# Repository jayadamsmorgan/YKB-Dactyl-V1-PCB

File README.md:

# YKB Skadi KiCad PCB files

## Project setup

```bash
git clone https://github.com/jayadamsmorgan/ykb-skadi-pcb
cd ykb-skadi-pcb
git submodule init
git submodule update
```

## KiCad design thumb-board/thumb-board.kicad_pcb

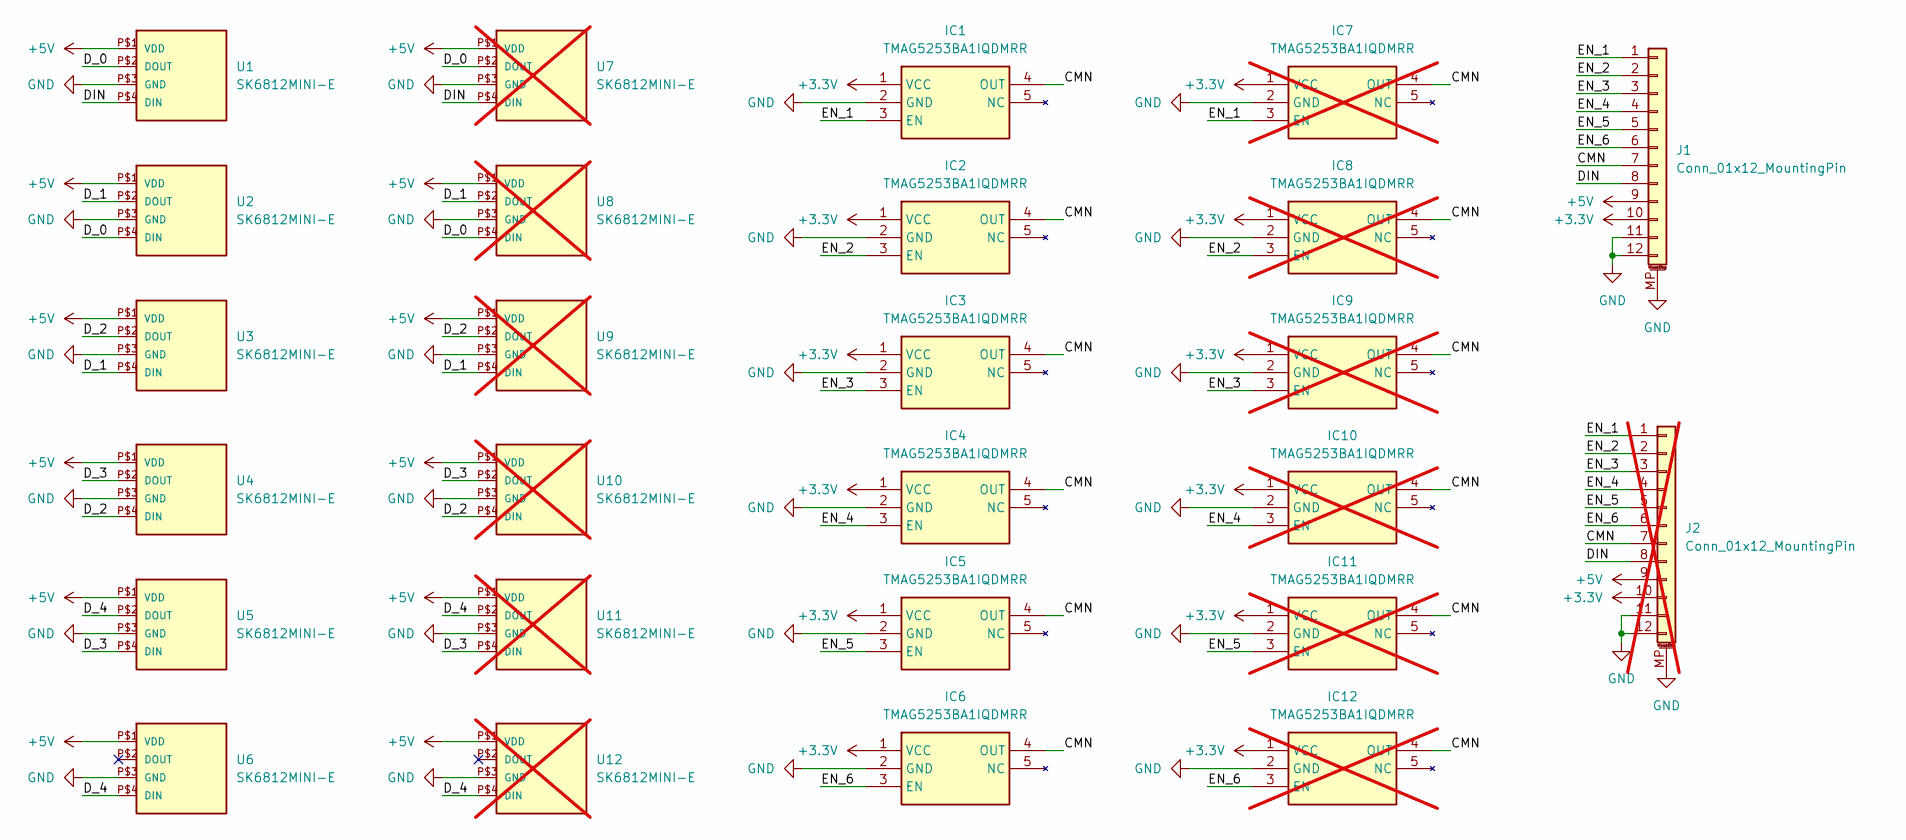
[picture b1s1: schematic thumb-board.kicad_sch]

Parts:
IC1, IC2, IC3, IC4, IC5, IC6: TMAG5253BA1IQDMRR; Mouser Part Number 595-TMAG5253BA1IQDMR
IC7, IC8, IC9, IC10, IC11, IC12: TMAG5253BA1IQDMRR; Mouser Part Number 595-TMAG5253BA1IQDMR; not fitted
J1: Conn_01x12_MountingPin; JST_SH_BM12B-SRSS-TB_1x12-1MP_P1.00mm_Vertical
J2: Conn_01x12_MountingPin; JST_SH_BM12B-SRSS-TB_1x12-1MP_P1.00mm_Vertical; not fitted
U1, U2, U3, U4, U5, U6: SK6812MINI-E
U7, U8, U9, U10, U11, U12: SK6812MINI-E; not fitted

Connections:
+3.3V: IC1.1 (VCC), IC2.1 (VCC), IC3.1 (VCC), IC4.1 (VCC), IC5.1 (VCC), IC6.1 (VCC), IC7.1 (VCC), IC8.1 (VCC), IC9.1 (VCC), IC10.1 (VCC), IC11.1 (VCC), IC12.1 (VCC), J1.10, J2.10
+5V: J1.9, J2.9, U1.P$1 (VDD), U2.P$1 (VDD), U3.P$1 (VDD), U4.P$1 (VDD), U5.P$1 (VDD), U6.P$1 (VDD), U7.P$1 (VDD), U8.P$1 (VDD), U9.P$1 (VDD), U10.P$1 (VDD), U11.P$1 (VDD), U12.P$1 (VDD)
/CMN: IC1.4 (OUT), IC2.4 (OUT), IC3.4 (OUT), IC4.4 (OUT), IC5.4 (OUT), IC6.4 (OUT), IC7.4 (OUT), IC8.4 (OUT), IC9.4 (OUT), IC10.4 (OUT), IC11.4 (OUT), IC12.4 (OUT), J1.7, J2.7
/DIN: J1.8, J2.8, U1.P$4 (DIN), U7.P$4 (DIN)
/D_0: U1.P$2 (DOUT), U2.P$4 (DIN), U7.P$2 (DOUT), U8.P$4 (DIN)
/D_1: U2.P$2 (DOUT), U3.P$4 (DIN), U8.P$2 (DOUT), U9.P$4 (DIN)
/D_2: U3.P$2 (DOUT), U4.P$4 (DIN), U9.P$2 (DOUT), U10.P$4 (DIN)
/D_3: U4.P$2 (DOUT), U5.P$4 (DIN), U10.P$2 (DOUT), U11.P$4 (DIN)
/D_4: U5.P$2 (DOUT), U6.P$4 (DIN), U11.P$2 (DOUT), U12.P$4 (DIN)
/EN_1: IC1.3 (EN), IC7.3 (EN), J1.1, J2.1
/EN_2: IC2.3 (EN), IC8.3 (EN), J1.2, J2.2
/EN_3: IC3.3 (EN), IC9.3 (EN), J1.3, J2.3
/EN_4: IC4.3 (EN), IC10.3 (EN), J1.4, J2.4
/EN_5: IC5.3 (EN), IC11.3 (EN), J1.5, J2.5
/EN_6: IC6.3 (EN), IC12.3 (EN), J1.6, J2.6
GND: IC1.2 (GND), IC2.2 (GND), IC3.2 (GND), IC4.2 (GND), IC5.2 (GND), IC6.2 (GND), IC7.2 (GND), IC8.2 (GND), IC9.2 (GND), IC10.2 (GND), IC11.2 (GND), IC12.2 (GND), J1.11, J1.12, J1.MP (MountPin), J2.11, J2.12, J2.MP (MountPin), U1.P$3 (GND), U2.P$3 (GND), U3.P$3 (GND), U4.P$3 (GND), U5.P$3 (GND), U6.P$3 (GND), U7.P$3 (GND), U8.P$3 (GND), U9.P$3 (GND), U10.P$3 (GND), U11.P$3 (GND), U12.P$3 (GND)

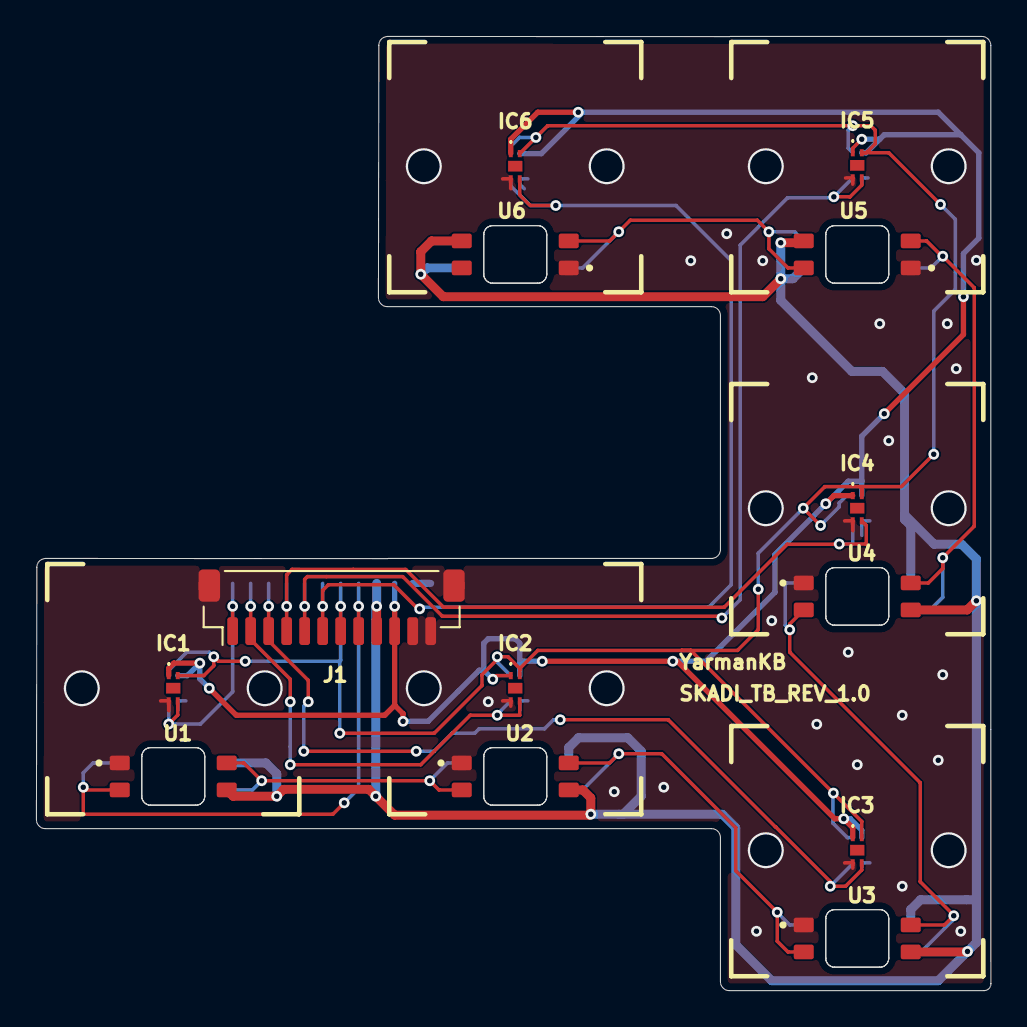
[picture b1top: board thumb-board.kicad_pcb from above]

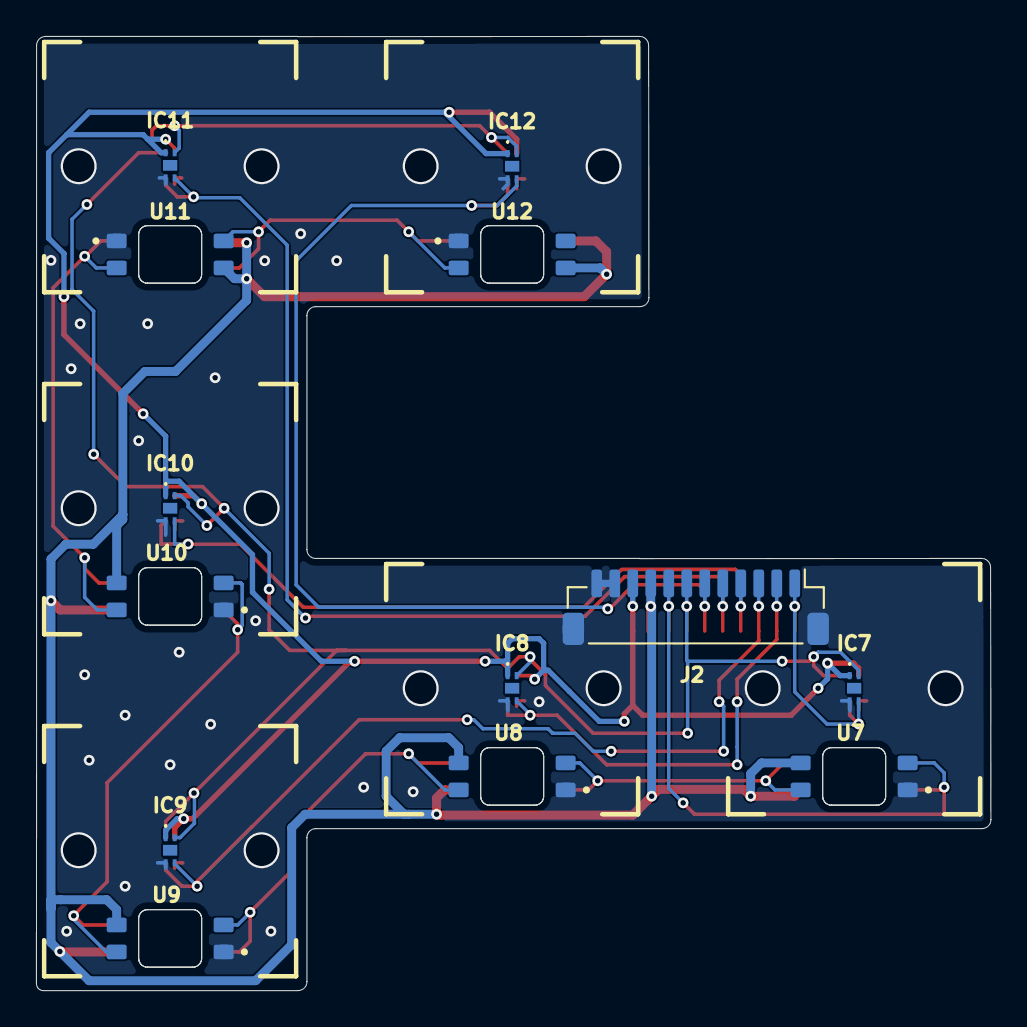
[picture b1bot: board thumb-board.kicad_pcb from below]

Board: 2 copper layers, 53.0 x 53.0 mm, 26 parts (13 on the bottom side), 16 nets.

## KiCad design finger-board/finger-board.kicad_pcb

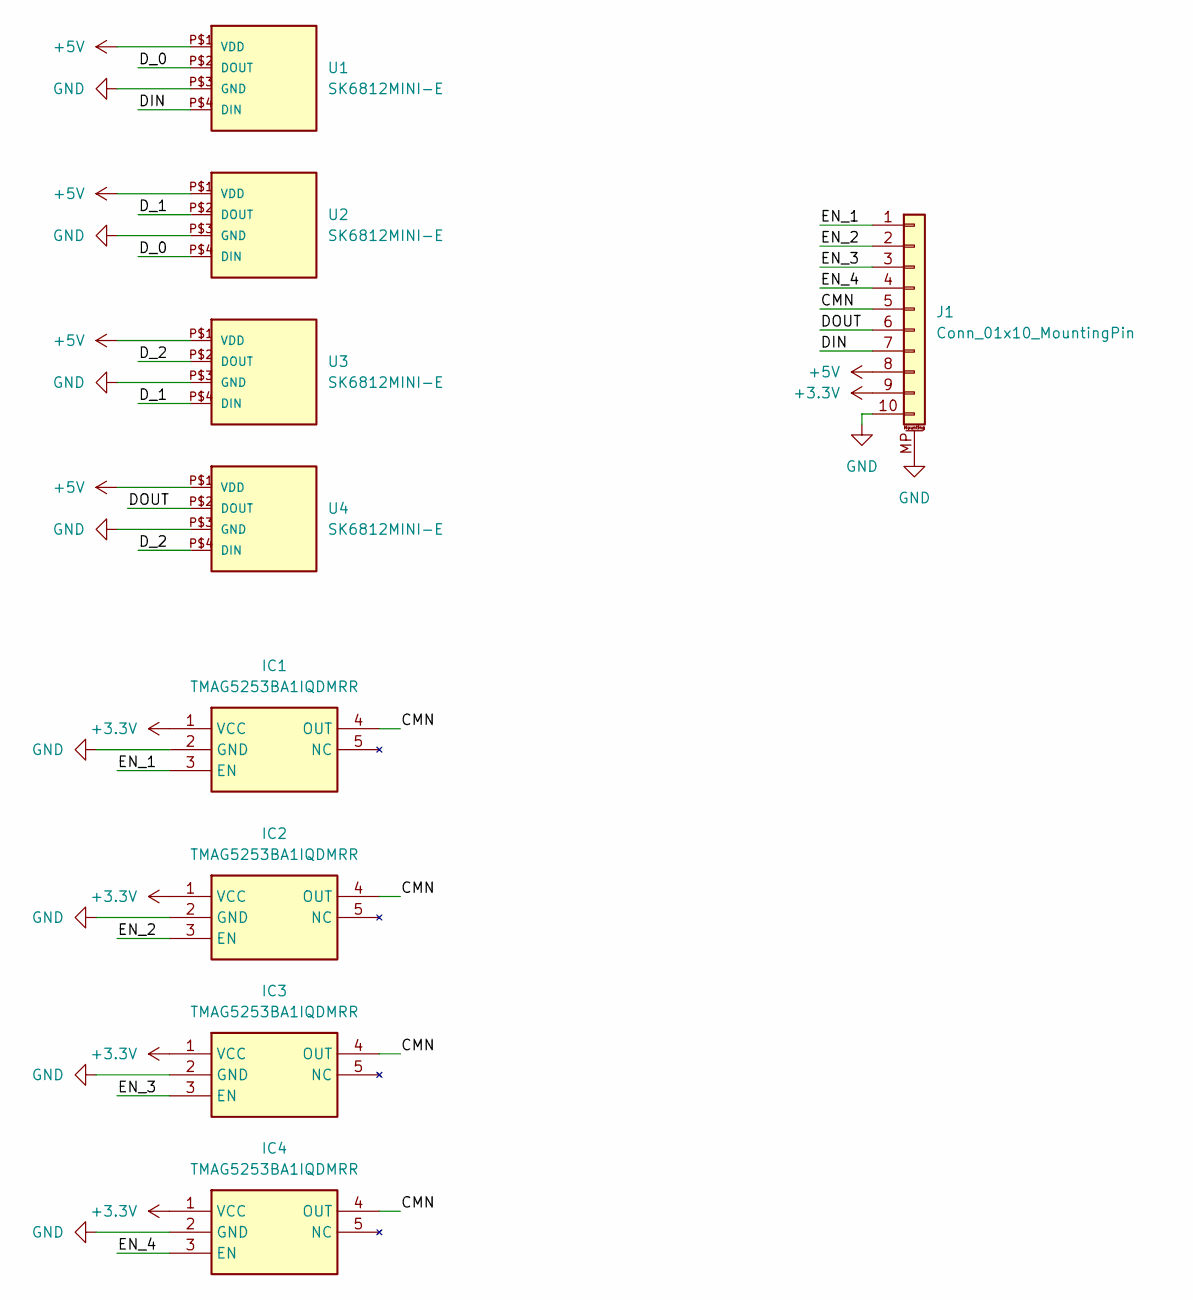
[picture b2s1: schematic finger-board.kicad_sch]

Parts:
IC1, IC2, IC3, IC4: TMAG5253BA1IQDMRR; Mouser Part Number 595-TMAG5253BA1IQDMR
J1: Conn_01x10_MountingPin; JST_SH_BM10B-SRSS-TB_1x10-1MP_P1.00mm_Vertical
U1, U2, U3, U4: SK6812MINI-E

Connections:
+3.3V: IC1.1 (VCC), IC2.1 (VCC), IC3.1 (VCC), IC4.1 (VCC), J1.9
+5V: J1.8, U1.P$1 (VDD), U2.P$1 (VDD), U3.P$1 (VDD), U4.P$1 (VDD)
/CMN: IC1.4 (OUT), IC2.4 (OUT), IC3.4 (OUT), IC4.4 (OUT), J1.5
/DIN: J1.7, U1.P$4 (DIN)
/DOUT: J1.6, U4.P$2 (DOUT)
/D_0: U1.P$2 (DOUT), U2.P$4 (DIN)
/D_1: U2.P$2 (DOUT), U3.P$4 (DIN)
/D_2: U3.P$2 (DOUT), U4.P$4 (DIN)
/EN_1: IC1.3 (EN), J1.1
/EN_2: IC2.3 (EN), J1.2
/EN_3: IC3.3 (EN), J1.3
/EN_4: IC4.3 (EN), J1.4
GND: IC1.2 (GND), IC2.2 (GND), IC3.2 (GND), IC4.2 (GND), J1.10, J1.MP (MountPin), U1.P$3 (GND), U2.P$3 (GND), U3.P$3 (GND), U4.P$3 (GND)

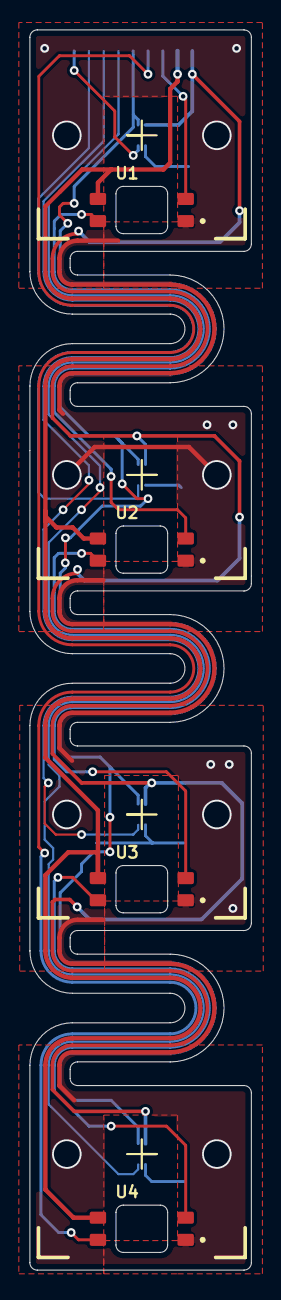
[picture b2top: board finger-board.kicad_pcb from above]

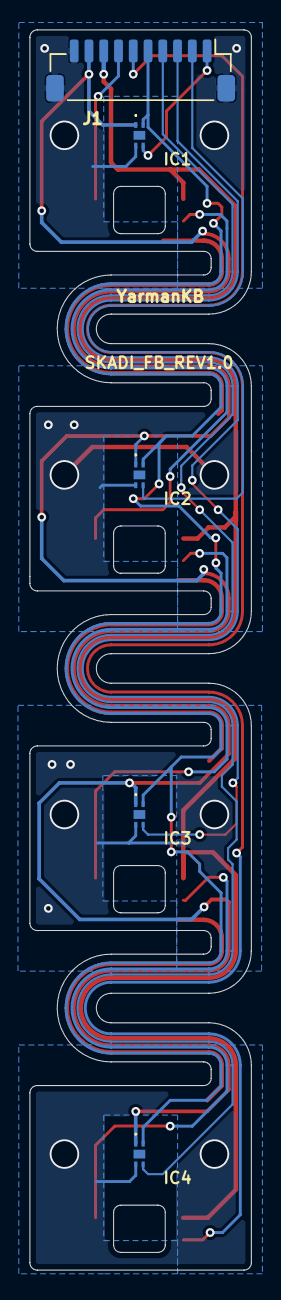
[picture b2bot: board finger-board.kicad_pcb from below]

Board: 2 copper layers, 15.0 x 84.0 mm, 9 parts (5 on the bottom side), 13 nets.

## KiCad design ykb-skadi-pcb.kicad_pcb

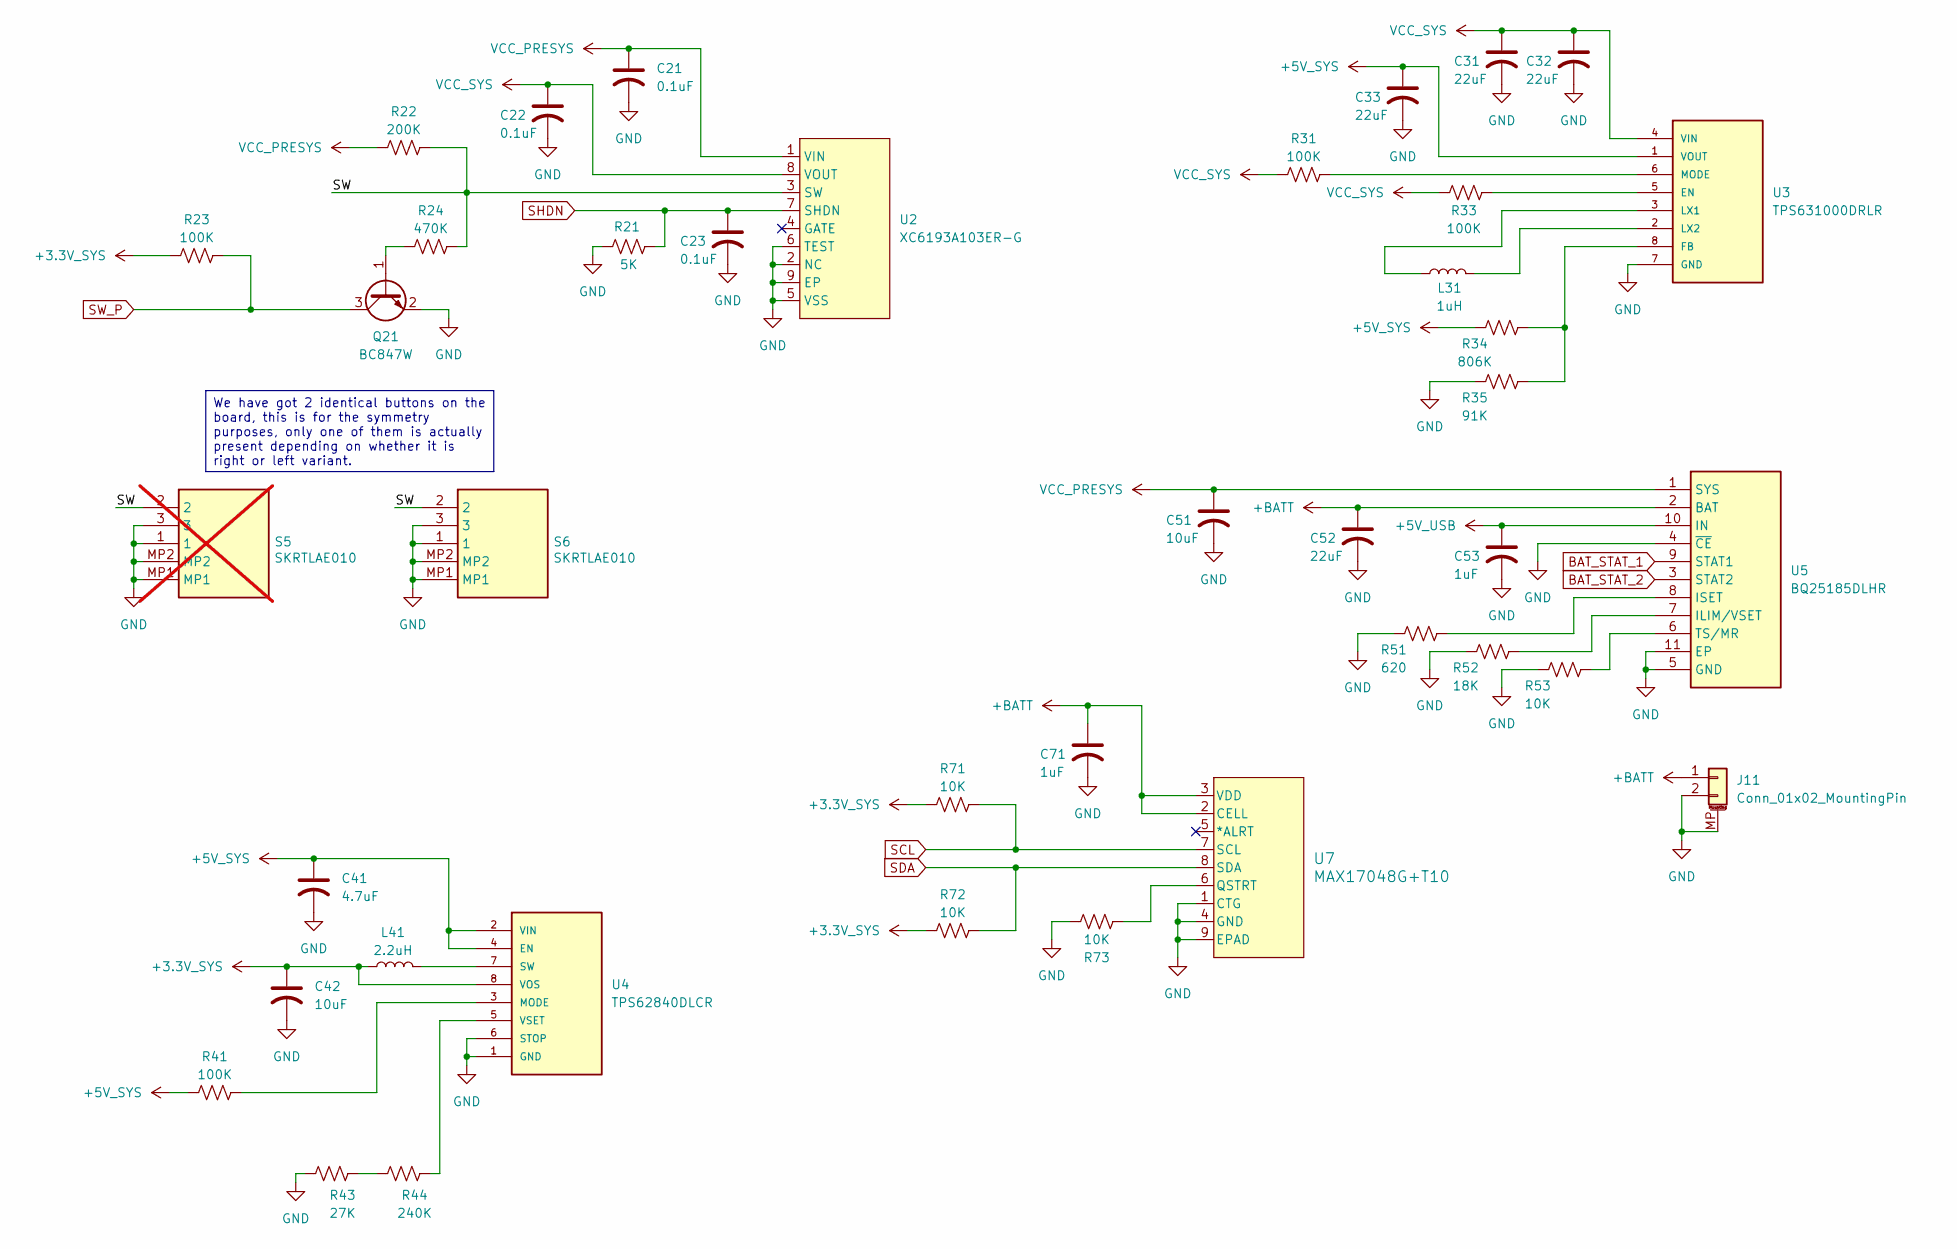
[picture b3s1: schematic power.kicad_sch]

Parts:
C21, C22, C23: 0.1uF; C_0402_1005Metric
C31, C32, C33, C52: 22uF; C_0402_1005Metric
C41: 4.7uF; C_0402_1005Metric
C42, C51: 10uF; C_0402_1005Metric
C53, C71: 1uF; C_0402_1005Metric
J11: Conn_01x02_MountingPin; JST_SHL_SM02B-SHLS-TF_1x02-1MP_P1.00mm_Horizontal
L31: 1uH; L_1008_2520Metric
L41: 2.2uH; L_Murata_DFE201610P
Q21: BC847W; SOT-323_SC-70
R21: 5K; R_0402_1005Metric
R22: 200K; R_0402_1005Metric
R23, R31, R33, R41: 100K; R_0402_1005Metric
R24: 470K; R_0402_1005Metric
R34: 806K; R_0402_1005Metric
R35: 91K; R_0402_1005Metric
R43: 27K; R_0402_1005Metric
R44: 240K; R_0402_1005Metric
R51: 620; R_0402_1005Metric
R52: 18K; R_0402_1005Metric
R53, R71, R72, R73: 10K; R_0402_1005Metric
S5: SKRTLAE010; Mouser Part Number 688-SKRTLA; not fitted
S6: SKRTLAE010; Mouser Part Number 688-SKRTLA
U2: XC6193A103ER-G; USP-8B06
U3: TPS631000DRLR; SOT50P160X60-8N; PARTREV B
U4: TPS62840DLCR; SON50P200X150X100-8N
U5: BQ25185DLHR; SON40P220X200X80-11N; Mouser Part Number 595-BQ25185DLHR
U7: MAX17048G+T10; 21-0168E_T822-3_MXM

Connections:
+3.3V_SYS: C42.1, L41.1, R23.2, R71.2, R72.2, U4.8 (VOS); also elsewhere on the board
+5V_SYS: C33.1, C41.1, R34.2, R41.2, U3.1 (VOUT), U4.2 (VIN), U4.4 (EN); also elsewhere on the board
+5V_USB: C53.1, U5.10 (IN); also elsewhere on the board
+BATT: C52.1, C71.1, J11.1, U5.2 (BAT), U7.2 (CELL), U7.3 (VDD)
/Power/SW: R22.1, R24.1, S5.2, S6.2, U2.3 (SW)
BAT_STAT_1: U5.9 (STAT1); also elsewhere on the board
BAT_STAT_2: U5.3 (STAT2); also elsewhere on the board
GND: C21.2, C22.2, C23.2, C31.2, C32.2, C33.2, C41.2, C42.2, C51.2, C52.2, C53.2, C71.2, J11.2, J11.MP (MountPin), Q21.2 (E), R21.2, R35.2, R43.2, R51.2, R52.2, R53.2, R73.1, S5.1, S5.3, S5.MP1, S5.MP2, S6.1, S6.3, S6.MP1, S6.MP2, U2.2 (NC), U2.5 (VSS), U2.6 (TEST), U2.9 (EP), U3.7 (GND), U4.1 (GND), U4.6 (STOP), U5.4 (~CE), U5.5 (GND), U5.11 (EP), U7.1 (CTG), U7.4 (GND), U7.9 (EPAD); also elsewhere on the board
unnamed: Q21.1 (B), R24.2
unnamed: R43.1, R44.2
unnamed: R33.1, U3.5 (EN)
unnamed: R34.1, R35.1, U3.8 (FB)
unnamed: L31.1, U3.3 (LX1)
unnamed: L31.2, U3.2 (LX2)
unnamed: R31.1, U3.6 (MODE)
unnamed: R41.1, U4.3 (MODE)
unnamed: L41.2, U4.7 (SW)
unnamed: R44.1, U4.5 (VSET)
unnamed: R52.1, U5.7 (ILIM/VSET)
unnamed: R51.1, U5.8 (ISET)
unnamed: R53.1, U5.6 (TS/MR)
unnamed: R73.2, U7.6 (QSTRT)
SCL: R71.1, U7.7 (SCL); also elsewhere on the board
SDA: R72.1, U7.8 (SDA); also elsewhere on the board
SHDN: C23.1, R21.1, U2.7 (SHDN); also elsewhere on the board
SW_P: Q21.3 (C), R23.1; also elsewhere on the board
VCC_PRESYS: C21.1, C51.1, R22.2, U2.1 (VIN), U5.1 (SYS); also elsewhere on the board
VCC_SYS: C22.1, C31.1, C32.1, R31.2, R33.2, U2.8 (VOUT), U3.4 (VIN)

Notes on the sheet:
We have got 2 identical buttons on the board, this is for the symmetry purposes, only one of them is actually present depending on whether it is right or left variant.

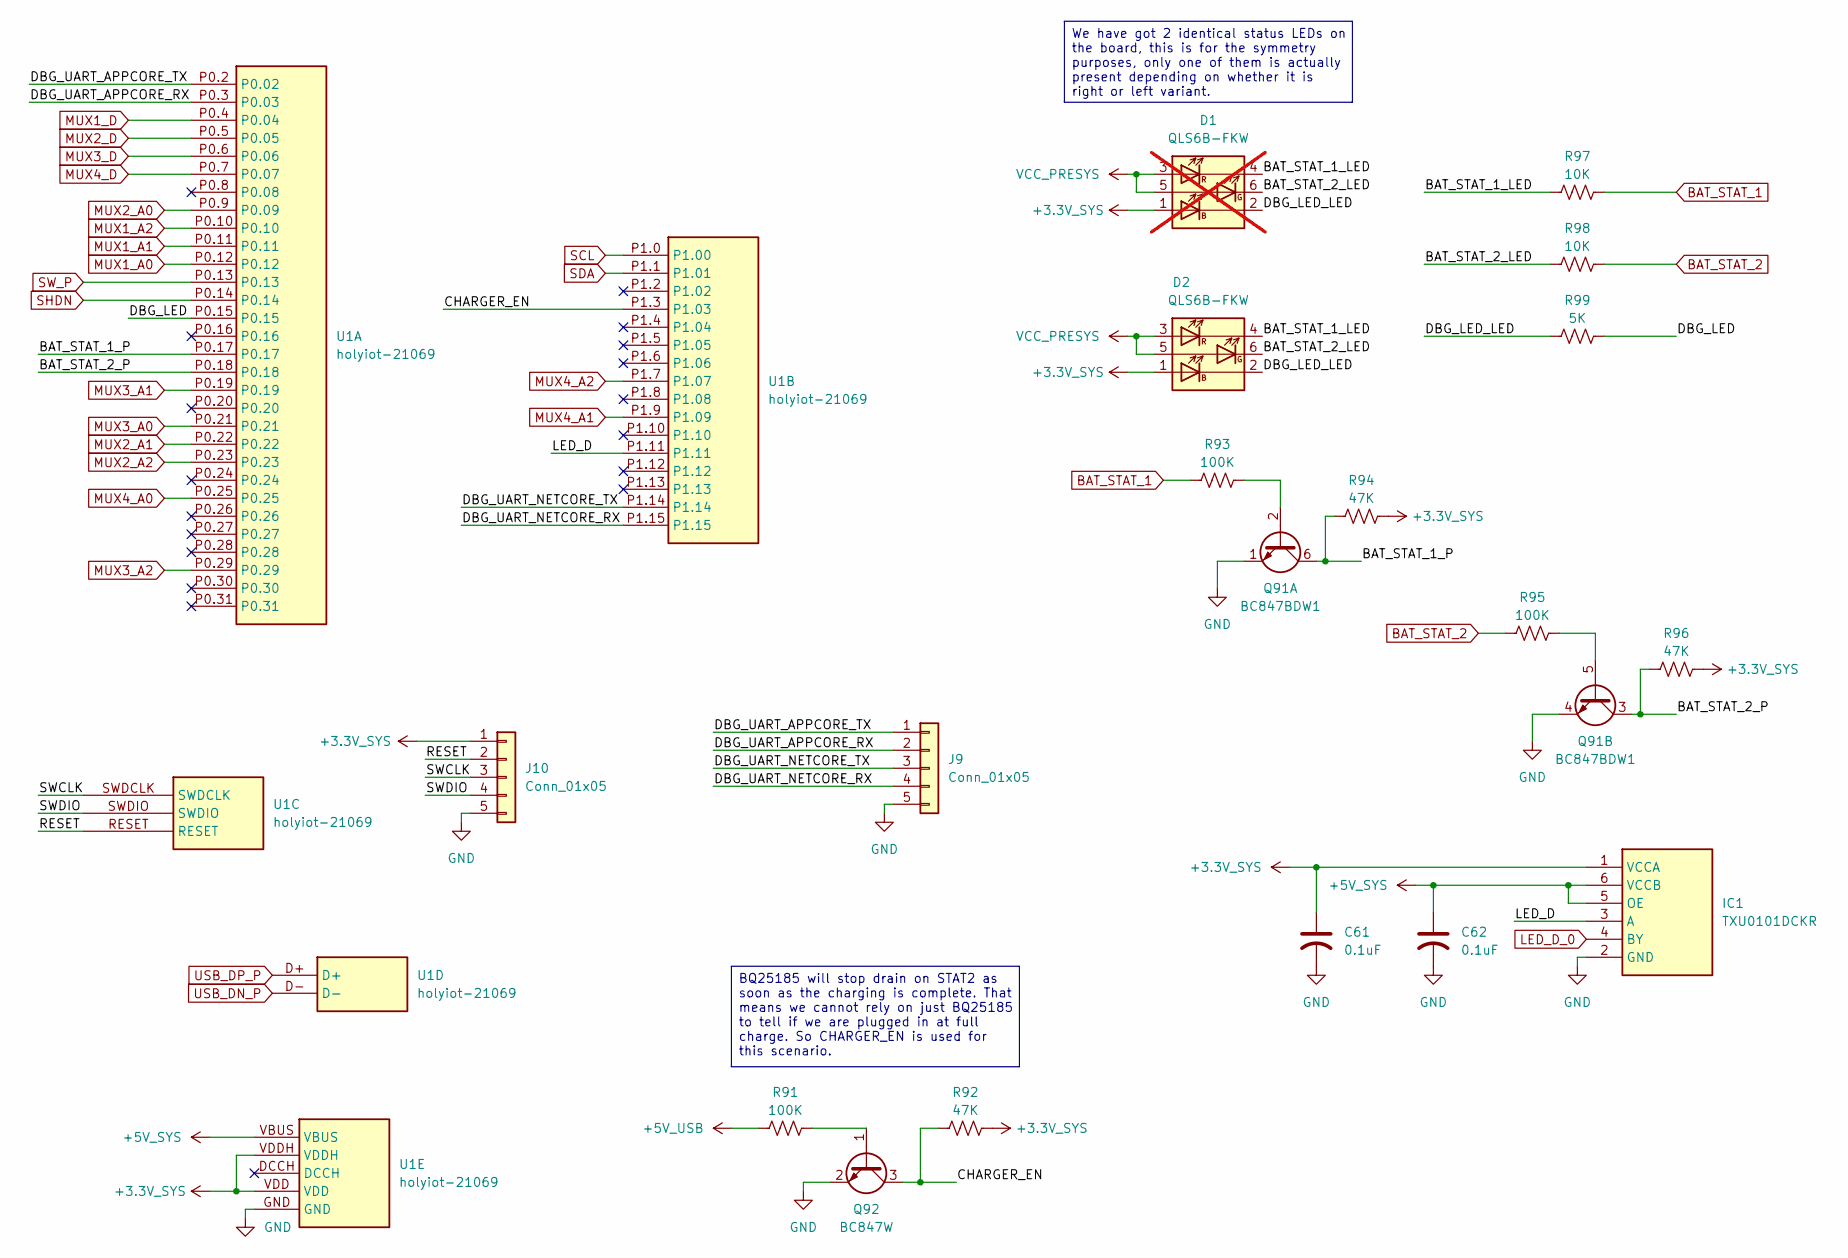
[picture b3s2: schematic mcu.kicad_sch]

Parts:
C61, C62: 0.1uF; C_0402_1005Metric
D1: QLS6B-FKW; LED_Cree-PLCC6_4.7x1.5mm; not fitted
D2: QLS6B-FKW; LED_Cree-PLCC6_4.7x1.5mm
IC1: TXU0101DCKR; SOT65P210X110-6N; Mouser Part Number 595-TXU0101DCKR
J9, J10: Conn_01x05; PinSocket_1x05_P2.54mm_Vertical
Q91: BC847BDW1; SOT-363_SC-70-6
Q92: BC847W; SOT-323_SC-70
R91, R93, R95: 100K; R_0402_1005Metric
R92, R94, R96: 47K; R_0402_1005Metric
R97, R98: 10K; R_0402_1005Metric
R99: 5K; R_0402_1005Metric
U1: holyiot-21069

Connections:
+3.3V_SYS: C61.1, D1.1 (AB), D2.1 (AB), IC1.1 (VCCA), J10.1, R92.1, R94.1, R96.1, U1.VDD, U1.VDDH; also elsewhere on the board
+5V_SYS: C62.1, IC1.5 (OE), IC1.6 (VCCB), U1.VBUS; also elsewhere on the board
+5V_USB: R91.2; also elsewhere on the board
/MCU/BAT_STAT_1_LED: D1.4 (KR), D2.4 (KR), R97.2
/MCU/BAT_STAT_1_P: Q91.6 (C1), R94.2, U1.P0.17
/MCU/BAT_STAT_2_LED: D1.6 (KR), D2.6 (KR), R98.2
/MCU/BAT_STAT_2_P: Q91.3 (C2), R96.2, U1.P0.18
/MCU/CHARGER_EN: Q92.3 (C), R92.2, U1.P1.3 (P1.03)
/MCU/DBG_LED: R99.1, U1.P0.15
/MCU/DBG_LED_LED: D1.2 (KB), D2.2 (KB), R99.2
/MCU/DBG_UART_APPCORE_RX: J9.2, U1.P0.3 (P0.03)
/MCU/DBG_UART_APPCORE_TX: J9.1, U1.P0.2 (P0.02)
/MCU/DBG_UART_NETCORE_RX: J9.4, U1.P1.15
/MCU/DBG_UART_NETCORE_TX: J9.3, U1.P1.14
/MCU/LED_D: IC1.3 (A), U1.P1.11
/MCU/RESET: J10.2, U1.RESET
/MCU/SWCLK: J10.3, U1.SWDCLK
/MCU/SWDIO: J10.4, U1.SWDIO
BAT_STAT_1: R93.2, R97.1; also elsewhere on the board
BAT_STAT_2: R95.2, R98.1; also elsewhere on the board
GND: C61.2, C62.2, IC1.2 (GND), J9.5, J10.5, Q91.1 (E1), Q91.4 (E2), Q92.2 (E), U1.GND; also elsewhere on the board
LED_D_0: IC1.4 (BY); also elsewhere on the board
MUX1_A0: U1.P0.12; also elsewhere on the board
MUX1_A1: U1.P0.11; also elsewhere on the board
MUX1_A2: U1.P0.10; also elsewhere on the board
MUX1_D: U1.P0.4 (P0.04); also elsewhere on the board
MUX2_A0: U1.P0.9 (P0.09); also elsewhere on the board
MUX2_A1: U1.P0.22; also elsewhere on the board
MUX2_A2: U1.P0.23; also elsewhere on the board
MUX2_D: U1.P0.5 (P0.05); also elsewhere on the board
MUX3_A0: U1.P0.21; also elsewhere on the board
MUX3_A1: U1.P0.19; also elsewhere on the board
MUX3_A2: U1.P0.29; also elsewhere on the board
MUX3_D: U1.P0.6 (P0.06); also elsewhere on the board
MUX4_A0: U1.P0.25; also elsewhere on the board
MUX4_A1: U1.P1.9 (P1.09); also elsewhere on the board
MUX4_A2: U1.P1.7 (P1.07); also elsewhere on the board
MUX4_D: U1.P0.7 (P0.07); also elsewhere on the board
unnamed: Q91.2 (B1), R93.1
unnamed: Q91.5 (B2), R95.1
unnamed: Q92.1 (B), R91.1
SCL: U1.P1.0 (P1.00); also elsewhere on the board
SDA: U1.P1.1 (P1.01); also elsewhere on the board
SHDN: U1.P0.14; also elsewhere on the board
SW_P: U1.P0.13; also elsewhere on the board
USB_DN_P: U1.D-; also elsewhere on the board
USB_DP_P: U1.D+; also elsewhere on the board
VCC_PRESYS: D1.3 (AR), D1.5 (AG), D2.3 (AR), D2.5 (AG); also elsewhere on the board

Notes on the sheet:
We have got 2 identical status LEDs on the board, this is for the symmetry purposes, only one of them is actually present depending on whether it is right or left variant.
BQ25185 will stop drain on STAT2 as soon as the charging is complete. That means we cannot rely on just BQ25185 to tell if we are plugged in at full charge. So CHARGER_EN is used for this scenario.

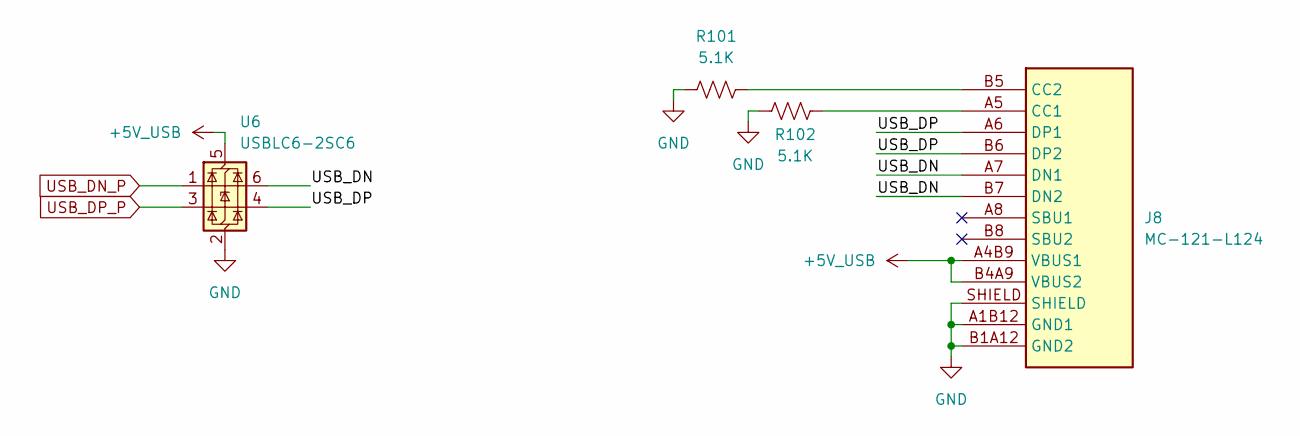
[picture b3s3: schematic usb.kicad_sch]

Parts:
J8: MC-121-L124
R101, R102: 5.1K; R_0402_1005Metric
U6: USBLC6-2SC6; SOT-23-6

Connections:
+5V_USB: J8.A4B9 (VBUS1), J8.B4A9 (VBUS2), U6.5 (VBUS); also elsewhere on the board
/USB/USB_DN: J8.A7 (DN1), J8.B7 (DN2), U6.6 (I/O1)
/USB/USB_DP: J8.A6 (DP1), J8.B6 (DP2), U6.4 (I/O2)
GND: J8.A1B12 (GND1), J8.B1A12 (GND2), J8.SHIELD, R101.2, R102.2, U6.2 (GND); also elsewhere on the board
unnamed: J8.A5 (CC1), R102.1
unnamed: J8.B5 (CC2), R101.1
USB_DN_P: U6.1 (I/O1); also elsewhere on the board
USB_DP_P: U6.3 (I/O2); also elsewhere on the board

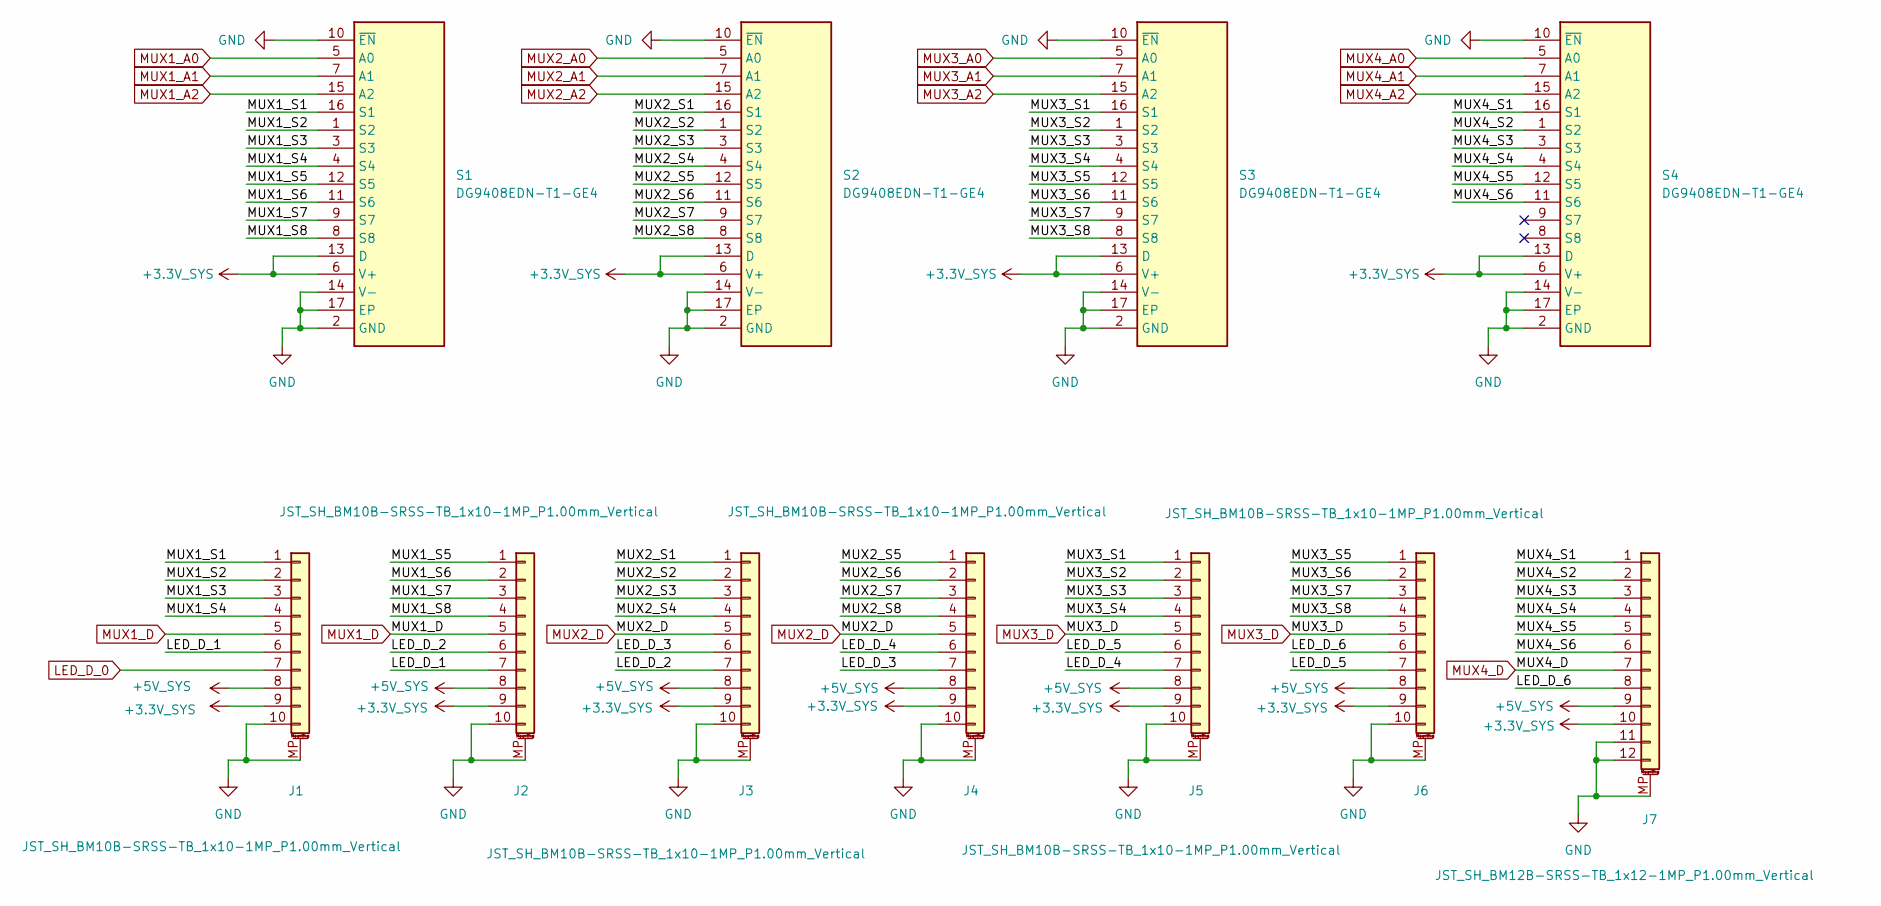
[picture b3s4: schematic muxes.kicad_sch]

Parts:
J1, J2, J3, J4, J5, J6: JST_SH_BM10B-SRSS-TB_1x10-1MP_P1.00mm_Vertical
J7: JST_SH_BM12B-SRSS-TB_1x12-1MP_P1.00mm_Vertical
S1, S2, S3, S4: DG9408EDN-T1-GE4; QFN65P400X400X95-17N-D; Mouser Part Number 78-DG9408EDN-T1-GE4

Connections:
+3.3V_SYS: J1.9, J2.9, J3.9, J4.9, J5.9, J6.9, J7.10, S1.6 (V+), S1.13 (D), S2.6 (V+), S2.13 (D), S3.6 (V+), S3.13 (D), S4.6 (V+), S4.13 (D); also elsewhere on the board
+5V_SYS: J1.8, J2.8, J3.8, J4.8, J5.8, J6.8, J7.9; also elsewhere on the board
/MUXes/LED_D_1: J1.6, J2.7
/MUXes/LED_D_2: J2.6, J3.7
/MUXes/LED_D_3: J3.6, J4.7
/MUXes/LED_D_4: J4.6, J5.7
/MUXes/LED_D_5: J5.6, J6.7
/MUXes/LED_D_6: J6.6, J7.8
/MUXes/MUX1_S1: J1.1, S1.16 (S1)
/MUXes/MUX1_S2: J1.2, S1.1 (S2)
/MUXes/MUX1_S3: J1.3, S1.3 (S3)
/MUXes/MUX1_S4: J1.4, S1.4 (S4)
/MUXes/MUX1_S5: J2.1, S1.12 (S5)
/MUXes/MUX1_S6: J2.2, S1.11 (S6)
/MUXes/MUX1_S7: J2.3, S1.9 (S7)
/MUXes/MUX1_S8: J2.4, S1.8 (S8)
/MUXes/MUX2_S1: J3.1, S2.16 (S1)
/MUXes/MUX2_S2: J3.2, S2.1 (S2)
/MUXes/MUX2_S3: J3.3, S2.3 (S3)
/MUXes/MUX2_S4: J3.4, S2.4 (S4)
/MUXes/MUX2_S5: J4.1, S2.12 (S5)
/MUXes/MUX2_S6: J4.2, S2.11 (S6)
/MUXes/MUX2_S7: J4.3, S2.9 (S7)
/MUXes/MUX2_S8: J4.4, S2.8 (S8)
/MUXes/MUX3_S1: J5.1, S3.16 (S1)
/MUXes/MUX3_S2: J5.2, S3.1 (S2)
/MUXes/MUX3_S3: J5.3, S3.3 (S3)
/MUXes/MUX3_S4: J5.4, S3.4 (S4)
/MUXes/MUX3_S5: J6.1, S3.12 (S5)
/MUXes/MUX3_S6: J6.2, S3.11 (S6)
/MUXes/MUX3_S7: J6.3, S3.9 (S7)
/MUXes/MUX3_S8: J6.4, S3.8 (S8)
/MUXes/MUX4_S1: J7.1, S4.16 (S1)
/MUXes/MUX4_S2: J7.2, S4.1 (S2)
/MUXes/MUX4_S3: J7.3, S4.3 (S3)
/MUXes/MUX4_S4: J7.4, S4.4 (S4)
/MUXes/MUX4_S5: J7.5, S4.12 (S5)
/MUXes/MUX4_S6: J7.6, S4.11 (S6)
GND: J1.10, J1.MP (MountPin), J2.10, J2.MP (MountPin), J3.10, J3.MP (MountPin), J4.10, J4.MP (MountPin), J5.10, J5.MP (MountPin), J6.10, J6.MP (MountPin), J7.11, J7.12, J7.MP (MountPin), S1.2 (GND), S1.10 (~EN), S1.14 (V-), S1.17 (EP), S2.2 (GND), S2.10 (~EN), S2.14 (V-), S2.17 (EP), S3.2 (GND), S3.10 (~EN), S3.14 (V-), S3.17 (EP), S4.2 (GND), S4.10 (~EN), S4.14 (V-), S4.17 (EP); also elsewhere on the board
LED_D_0: J1.7; also elsewhere on the board
MUX1_A0: S1.5 (A0); also elsewhere on the board
MUX1_A1: S1.7 (A1); also elsewhere on the board
MUX1_A2: S1.15 (A2); also elsewhere on the board
MUX1_D: J1.5, J2.5; also elsewhere on the board
MUX2_A0: S2.5 (A0); also elsewhere on the board
MUX2_A1: S2.7 (A1); also elsewhere on the board
MUX2_A2: S2.15 (A2); also elsewhere on the board
MUX2_D: J3.5, J4.5; also elsewhere on the board
MUX3_A0: S3.5 (A0); also elsewhere on the board
MUX3_A1: S3.7 (A1); also elsewhere on the board
MUX3_A2: S3.15 (A2); also elsewhere on the board
MUX3_D: J5.5, J6.5; also elsewhere on the board
MUX4_A0: S4.5 (A0); also elsewhere on the board
MUX4_A1: S4.7 (A1); also elsewhere on the board
MUX4_A2: S4.15 (A2); also elsewhere on the board
MUX4_D: J7.7; also elsewhere on the board

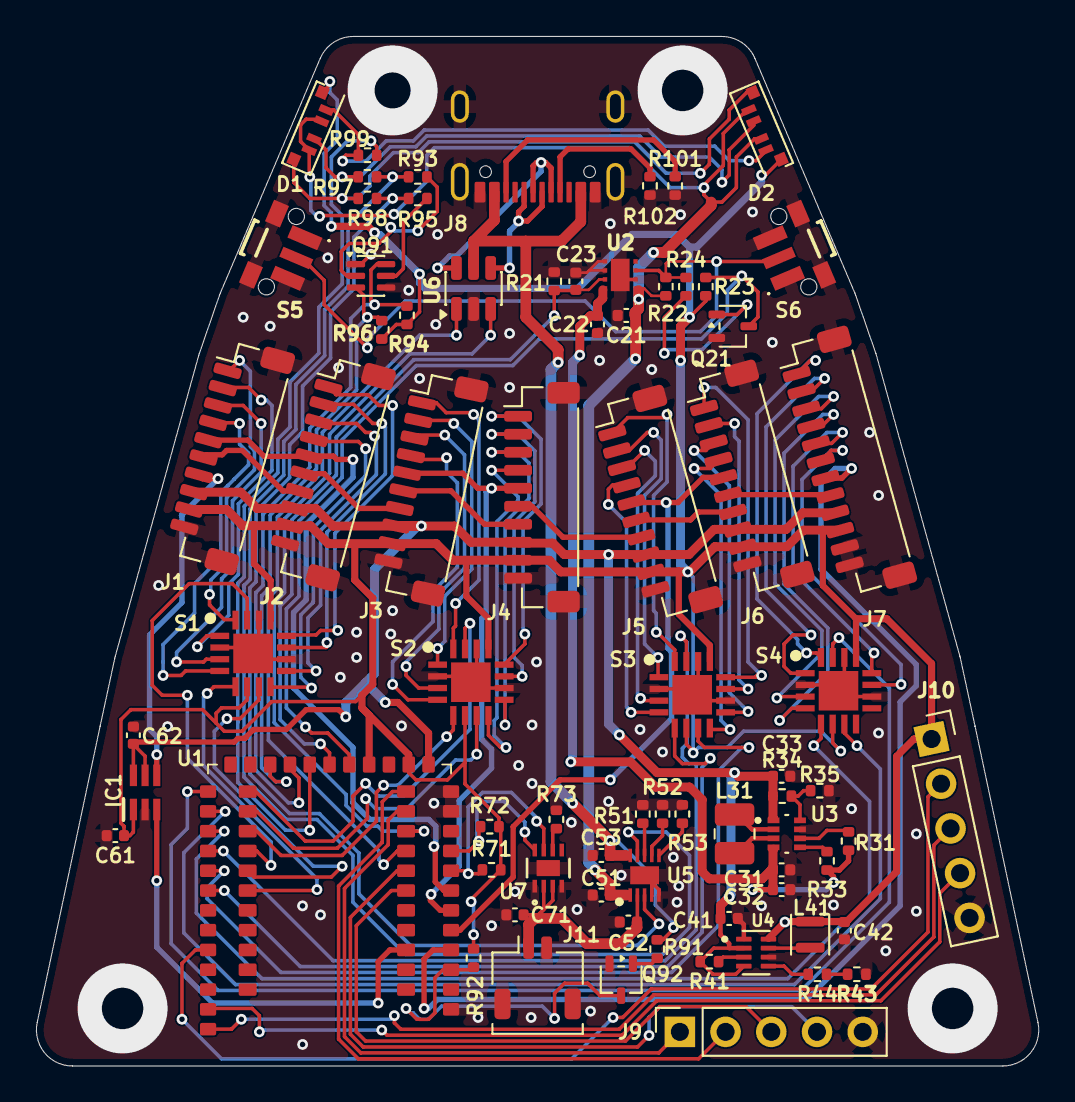
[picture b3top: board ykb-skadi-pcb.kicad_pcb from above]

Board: 2 copper layers, 55.7 x 57.2 mm, 74 parts (0 on the bottom side), 105 nets.

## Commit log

2026-02-16 Remove backups
2026-02-18 Modify placment of component
2026-02-18 Remove fp-info-cache & add .lck files to gitignore
2026-02-25 Add finger-board & thumb-board
2026-02-25 Add README
2026-02-26 Update kicad_lib
2026-02-26 Trace thumb-board
2026-03-01 Trace finger-board
2026-03-01 Update silkscreen text
2026-03-01 Add DRU
2026-03-01 Create LICENSE
2026-03-03 Fix board shape
2026-03-03 Fix global nets
2026-03-04 Place components
2026-03-17 Move SK6812 a bit down on daughter boards
2026-03-21 Trace the board
2026-03-21 Change PCB thickness to 1mm
2026-03-22 Change board thickness
2026-03-22 Add first version to the silkscreen
2026-04-11 Developer Preview 1
2026-04-22 Developer Preview 2
2026-04-22 Fix silkscreen for Developer Preview 2
2026-04-22 Tweak R23 and R24 values
2026-04-23 Refill zones
2026-05-04 Rename the board to Skadi
2026-05-04 Update LICENSE
